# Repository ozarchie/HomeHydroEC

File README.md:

# HomeHydroEC
=============
An extension of Michael Ratcliffe's excellent EC project.   
<B>See the Project Wiki for a full description.  </B>  
https://github.com/ozarchie/HomeHydroEC/wiki  

## Extensions  
-------------
This project addresses the issue of polarization by implementing a square wave balanced resistor approach to measurement.  
An additional analog input channel is required.  
The 1k resistor is split in two as two 470R resistors and the probe inserted between the resistors.  
The voltage across the 470R sense resistor allows calculation of the sense current.  
The voltage across the prongs and the sense current allows determination of the electrical conductivity.  
An 18B20 sensor is connected to monitor the solution temperature.  

Testing and documentation is underway. Documentation is included in the code.  

The Kcell of the probe is calculated using standard formula and measurements of the AC probe. 
EC Measurements agree well with Chinese TDC&EC meters.  
See the Project Wiki for a full description.  

## Original Work  

Original ideas and program published by -:  

www.MichaelRatcliffe.com/projects  
https://www.element14.com/community/community/design-challenges/vertical-farming/blog/2015/09/13/automated-green-house-blogs-main-page  
 
  28/8/2015  Michael Ratcliffe  Mike@MichaelRatcliffe.com

   This program is free software: you can redistribute it and/or modify
    it under the terms of the GNU General Public License as published by
    the Free Software Foundation, either version 3 of the License, or
    (at your option) any later version.

    This program is distributed in the hope that it will be useful,
    but WITHOUT ANY WARRANTY; without even the implied warranty of
    MERCHANTABILITY or FITNESS FOR A PARTICULAR PURPOSE.  See the
    GNU General Public License for more details.

    You should have received a copy of the GNU General Public License
    along with this program.  If not, see <http://www.gnu.org/licenses/>.

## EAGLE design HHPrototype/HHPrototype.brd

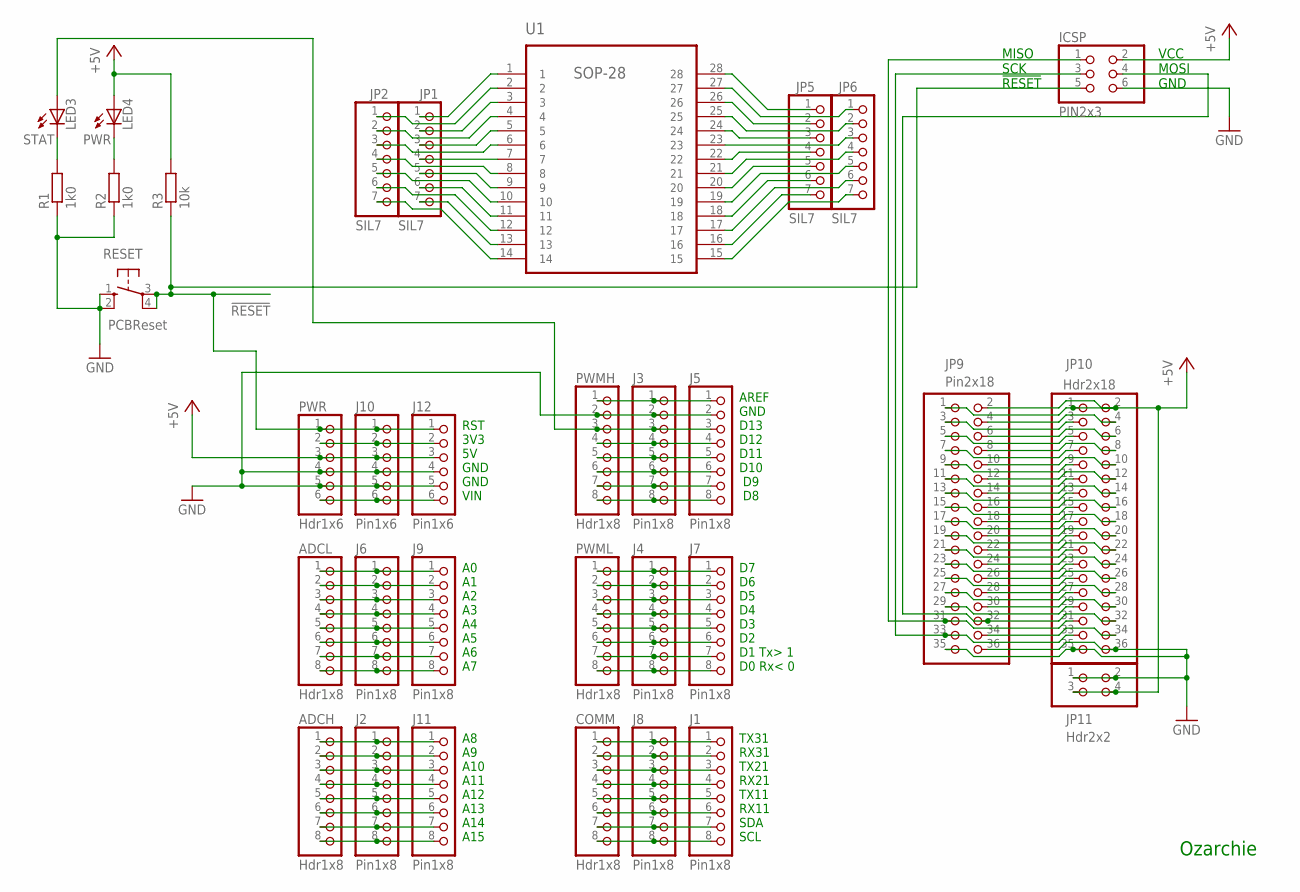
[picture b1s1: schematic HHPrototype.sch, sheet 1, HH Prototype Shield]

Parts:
ADCH: Hdr1x8; 1X08
ADCL: Hdr1x8; 1X08
COMM: Hdr1x8; 1X08
ICSP: PIN2x3; 2X03
J1, J2, J3, J4, J5, J6, J7, J8, J9, J11: Pin1x8; 1X08
J10, J12: Pin1x6; 1X06
JP1, JP2, JP5, JP6: SIL7; 1X07
JP9: Pin2x18; 2X18
JP10: Hdr2x18; 2X18
JP11: Hdr2x2; 2X02
LED3: STAT; CHIPLED_1206
LED4: PWR; CHIPLED_1206
PWMH: Hdr1x8; 1X08
PWML: Hdr1x8; 1X08
PWR: Hdr1x6; 1X06
R1, R2: 1k0; R0805
R3: 10k; R0805
RESET: PCBReset; B3F-10XX
U1: SOP-28; SOP50P1030X264-28N

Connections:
3V3: J10.2, J12.2, PWR.2
!RESET!: ICSP.5, J10.1, J12.1, PWR.1, R3.1, RESET.3, RESET.4 (P1)
+5V: ICSP.2, J10.3, J12.3, JP9.1, JP9.2, JP10.1, JP10.2, JP11.3, JP11.4, LED4.A, PWR.3, R3.2; also elsewhere on the board
A0: ADCL.1, J6.1, J9.1
A1: ADCL.2, J6.2, J9.2
A2: ADCL.3, J6.3, J9.3
A3: ADCL.4, J6.4, J9.4
A4: ADCL.5, J6.5, J9.5
A5: ADCL.6, J6.6, J9.6
A6: ADCL.7, J6.7, J9.7
A7: ADCL.8, J6.8, J9.8
A8: ADCH.1, J2.1, J11.1
A9: ADCH.2, J2.2, J11.2
A10: ADCH.3, J2.3, J11.3
A11: ADCH.4, J2.4, J11.4
A12: ADCH.5, J2.5, J11.5
A13: ADCH.6, J2.6, J11.6
A14: ADCH.7, J2.7, J11.7
A15: ADCH.8, J2.8, J11.8
AREF: J3.1, J5.1, PWMH.1
D0/RX0: J4.8, J7.8, PWML.8
D1/TX0: J4.7, J7.7, PWML.7
D2PWM: J4.6, J7.6, PWML.6
D3PWM: J4.5, J7.5, PWML.5
D4PWM: J4.4, J7.4, PWML.4
D5PWM: J4.3, J7.3, PWML.3
D6PWM: J4.2, J7.2, PWML.2
D7PWM: J4.1, J7.1, PWML.1
D8PWM: J3.8, J5.8, PWMH.8
D9PWM: J3.7, J5.7, PWMH.7
D10PWM: J3.6, J5.6, PWMH.6
D11PWM: J3.5, J5.5, PWMH.5
D12PWM: J3.4, J5.4, PWMH.4
D13PWM: J3.3, J5.3, LED3.A, PWMH.3
D14/TX3: COMM.1, J1.1, J8.1
D15/RX3: COMM.2, J1.2, J8.2
D16/TX2: COMM.3, J1.3, J8.3
D17/RX2: COMM.4, J1.4, J8.4
D18/TX1: COMM.5, J1.5, J8.5
D19/RX1: COMM.6, J1.6, J8.6
D20/SDA: COMM.7, J1.7, J8.7
D21/SCL: COMM.8, J1.8, J8.8
D22: JP9.3, JP10.3
D23: JP9.4, JP10.4
D24: JP9.5, JP10.5
D25: JP9.6, JP10.6
D26: JP9.7, JP10.7
D27: JP9.8, JP10.8
D28: JP9.9, JP10.9
D29: JP9.10, JP10.10
D30: JP9.11, JP10.11
D31: JP9.12, JP10.12
D32: JP9.13, JP10.13
D33: JP9.14, JP10.14
D34: JP9.15, JP10.15
D35: JP9.16, JP10.16
D36: JP9.17, JP10.17
D37: JP9.18, JP10.18
D38: JP9.19, JP10.19
D39: JP9.20, JP10.20
D40: JP9.21, JP10.21
D41: JP9.22, JP10.22
D42: JP9.23, JP10.23
D43: JP9.24, JP10.24
D44: JP9.25, JP10.25
D45: JP9.26, JP10.26
D46: JP9.27, JP10.27
D47: JP9.28, JP10.28
D48: JP9.29, JP10.29
D49: JP9.30, JP10.30
D53: JP9.34, JP10.34
GND: ICSP.6, J3.2, J5.2, J10.4, J10.5, J12.4, J12.5, JP9.35, JP9.36, JP10.35, JP10.36, JP11.1, JP11.2, PWMH.2, PWR.4, PWR.5, R1.1, R2.1, RESET.1 (S), RESET.2 (S1); also elsewhere on the board
MISO: ICSP.1, JP9.31, JP10.31
MOSI: ICSP.4, JP9.32, JP10.32
unnamed: LED3.C, R1.2
unnamed: LED4.C, R2.2
SCK: ICSP.3, JP9.33, JP10.33
SO1: JP1.1, U1.1
SO2: JP2.1, U1.2
SO3: JP1.2, U1.3
SO4: JP2.2, U1.4
SO5: JP1.3, U1.5
SO6: JP2.3, U1.6
SO7: JP1.4, U1.7
SO8: JP2.4, U1.8
SO9: JP1.5, U1.9
SO10: JP2.5, U1.10
SO11: JP1.6, U1.11
SO12: JP2.6, U1.12
SO13: JP1.7, U1.13
SO14: JP2.7, U1.14
SO15: JP6.7, U1.15
SO16: JP5.7, U1.16
SO17: JP6.6, U1.17
SO18: JP5.6, U1.18
SO19: JP6.5, U1.19
SO20: JP5.5, U1.20
SO21: JP6.4, U1.21
SO22: JP5.4, U1.22
SO23: JP6.3, U1.23
SO24: JP5.3, U1.24
SO25: JP6.2, U1.25
SO26: JP5.2, U1.26
SO27: JP6.1, U1.27
SO28: JP5.1, U1.28
VIN: J10.6, J12.6, PWR.6

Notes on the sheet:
RST 3V3 5V GND GND VIN
MISO SCK !RESET!
VCC MOSI GND
AREF GND D13 D12 D11 D10 D9 D8
D7 D6 D5 D4 D3 D2 D1 Tx> 1 D0 Rx< 0
A0 A1 A2 A3 A4 A5 A6 A7
A8 A9 A10 A11 A12 A13 A14 A15
TX31 RX31 TX21 RX21 TX11 RX11 SDA SCL
Ozarchie

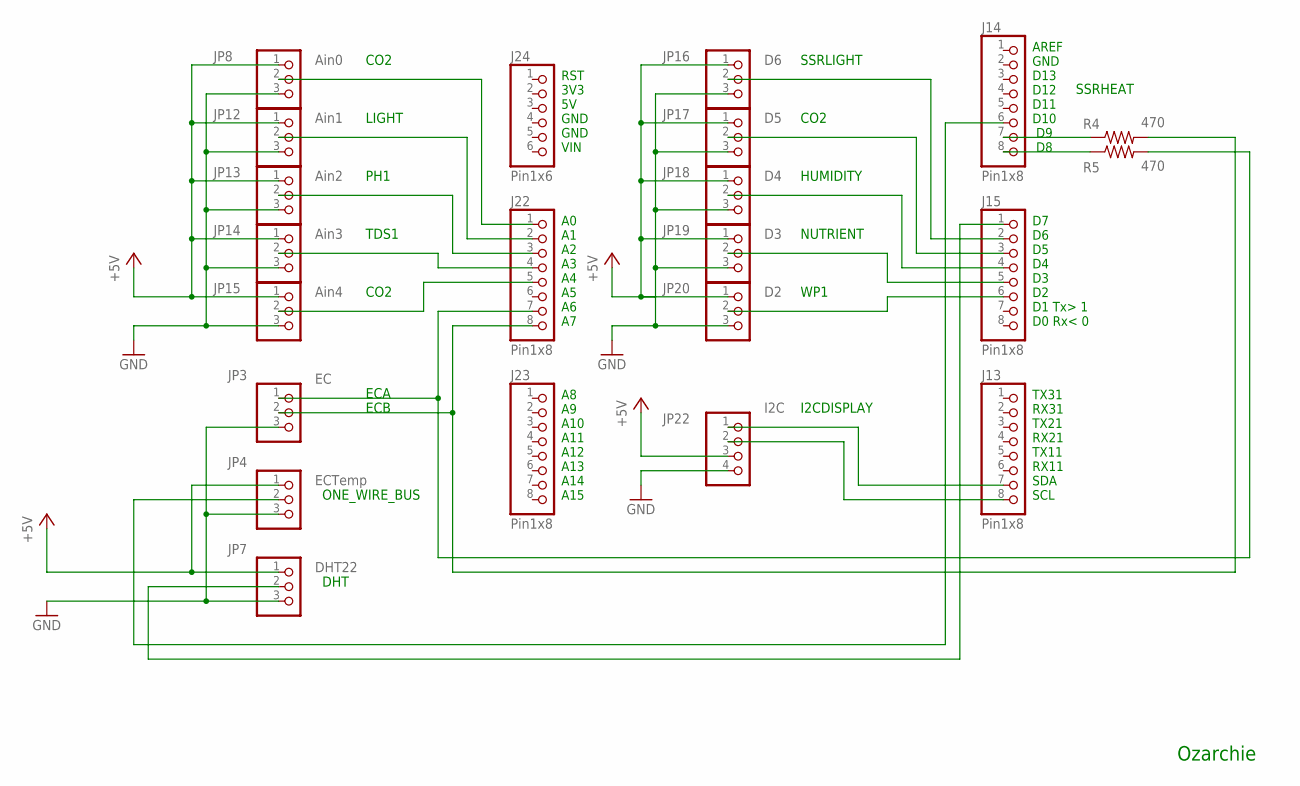
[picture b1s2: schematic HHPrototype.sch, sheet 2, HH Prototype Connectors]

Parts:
J13, J14, J15, J22, J23: Pin1x8; 1X08
J24: Pin1x6; 1X06
JP3: EC; 1X03
JP4: ECTemp; 1X03
JP7: DHT22; 1X03
JP8: Ain0; 1X03
JP12: Ain1; 1X03
JP13: Ain2; 1X03
JP14: Ain3; 1X03
JP15: Ain4; 1X03
JP16: D6; 1X03
JP17: D5; 1X03
JP18: D4; 1X03
JP19: D3; 1X03
JP20: D2; 1X03
JP22: I2C; 1X04
R4, R5: 470; 0207/2V

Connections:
+5V: JP4.1, JP7.1, JP8.1, JP12.1, JP13.1, JP14.1, JP15.1, JP16.1, JP17.1, JP18.1, JP19.1, JP20.1, JP22.3; also elsewhere on the board
GND: JP3.3, JP4.3, JP7.3, JP8.3, JP12.3, JP13.3, JP14.3, JP15.3, JP16.3, JP17.3, JP18.3, JP19.3, JP20.3, JP22.4; also elsewhere on the board
unnamed: J22.7, JP3.1, R5.2
unnamed: J15.6, JP20.2
unnamed: J15.5, JP19.2
unnamed: J15.4, JP18.2
unnamed: J15.3, JP17.2
unnamed: J15.2, JP16.2
unnamed: J22.1, JP8.2
unnamed: J22.2, JP12.2
unnamed: J22.3, JP13.2
unnamed: J22.4, JP14.2
unnamed: J22.5, JP15.2
unnamed: J13.7, JP22.1
unnamed: J13.8, JP22.2
unnamed: J15.1, JP7.2
unnamed: J22.8, JP3.2, R4.2
unnamed: J14.7, R4.1
unnamed: J14.6, JP4.2
unnamed: J14.8, R5.1

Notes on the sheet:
RST 3V3 5V GND GND VIN
A0 A1 A2 A3 A4 A5 A6 A7
A8 A9 A10 A11 A12 A13 A14 A15
Ozarchie
AREF GND D13 D12 D11 D10 D9 D8
D7 D6 D5 D4 D3 D2 D1 Tx> 1 D0 Rx< 0
TX31 RX31 TX21 RX21 TX11 RX11 SDA SCL
CO2
LIGHT
PH1
TDS1
ECA
ECB
SSRLIGHT
HUMIDITY
NUTRIENT
WP1
SSRHEAT
ONE_WIRE_BUS
DHT
I2CDISPLAY

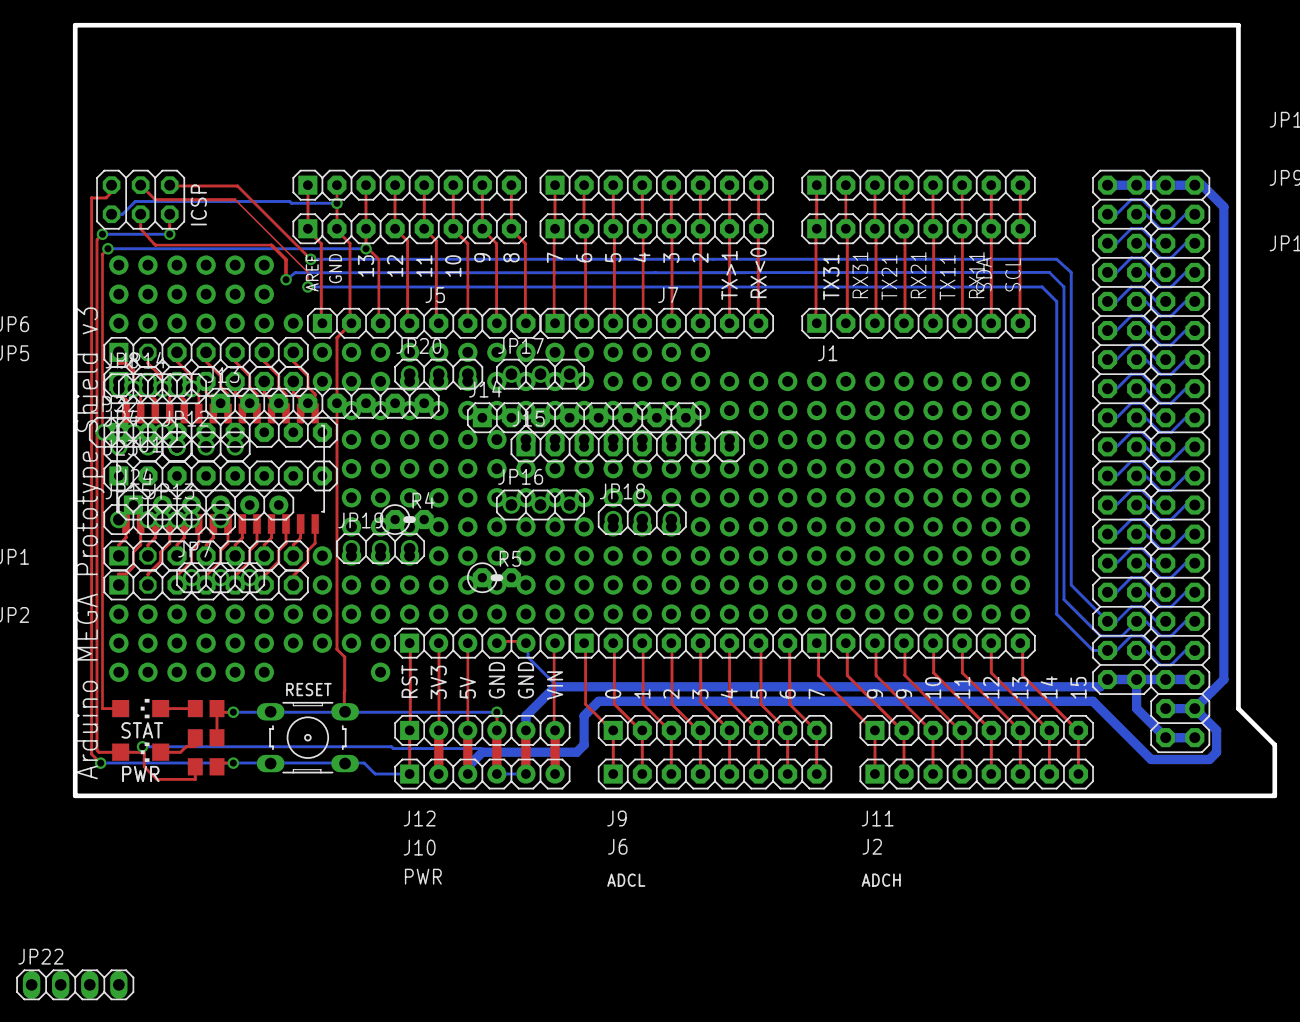
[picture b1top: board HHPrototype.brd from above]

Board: 2 copper layers, 104.8 x 67.3 mm, 55 parts (0 on the bottom side), 124 nets.

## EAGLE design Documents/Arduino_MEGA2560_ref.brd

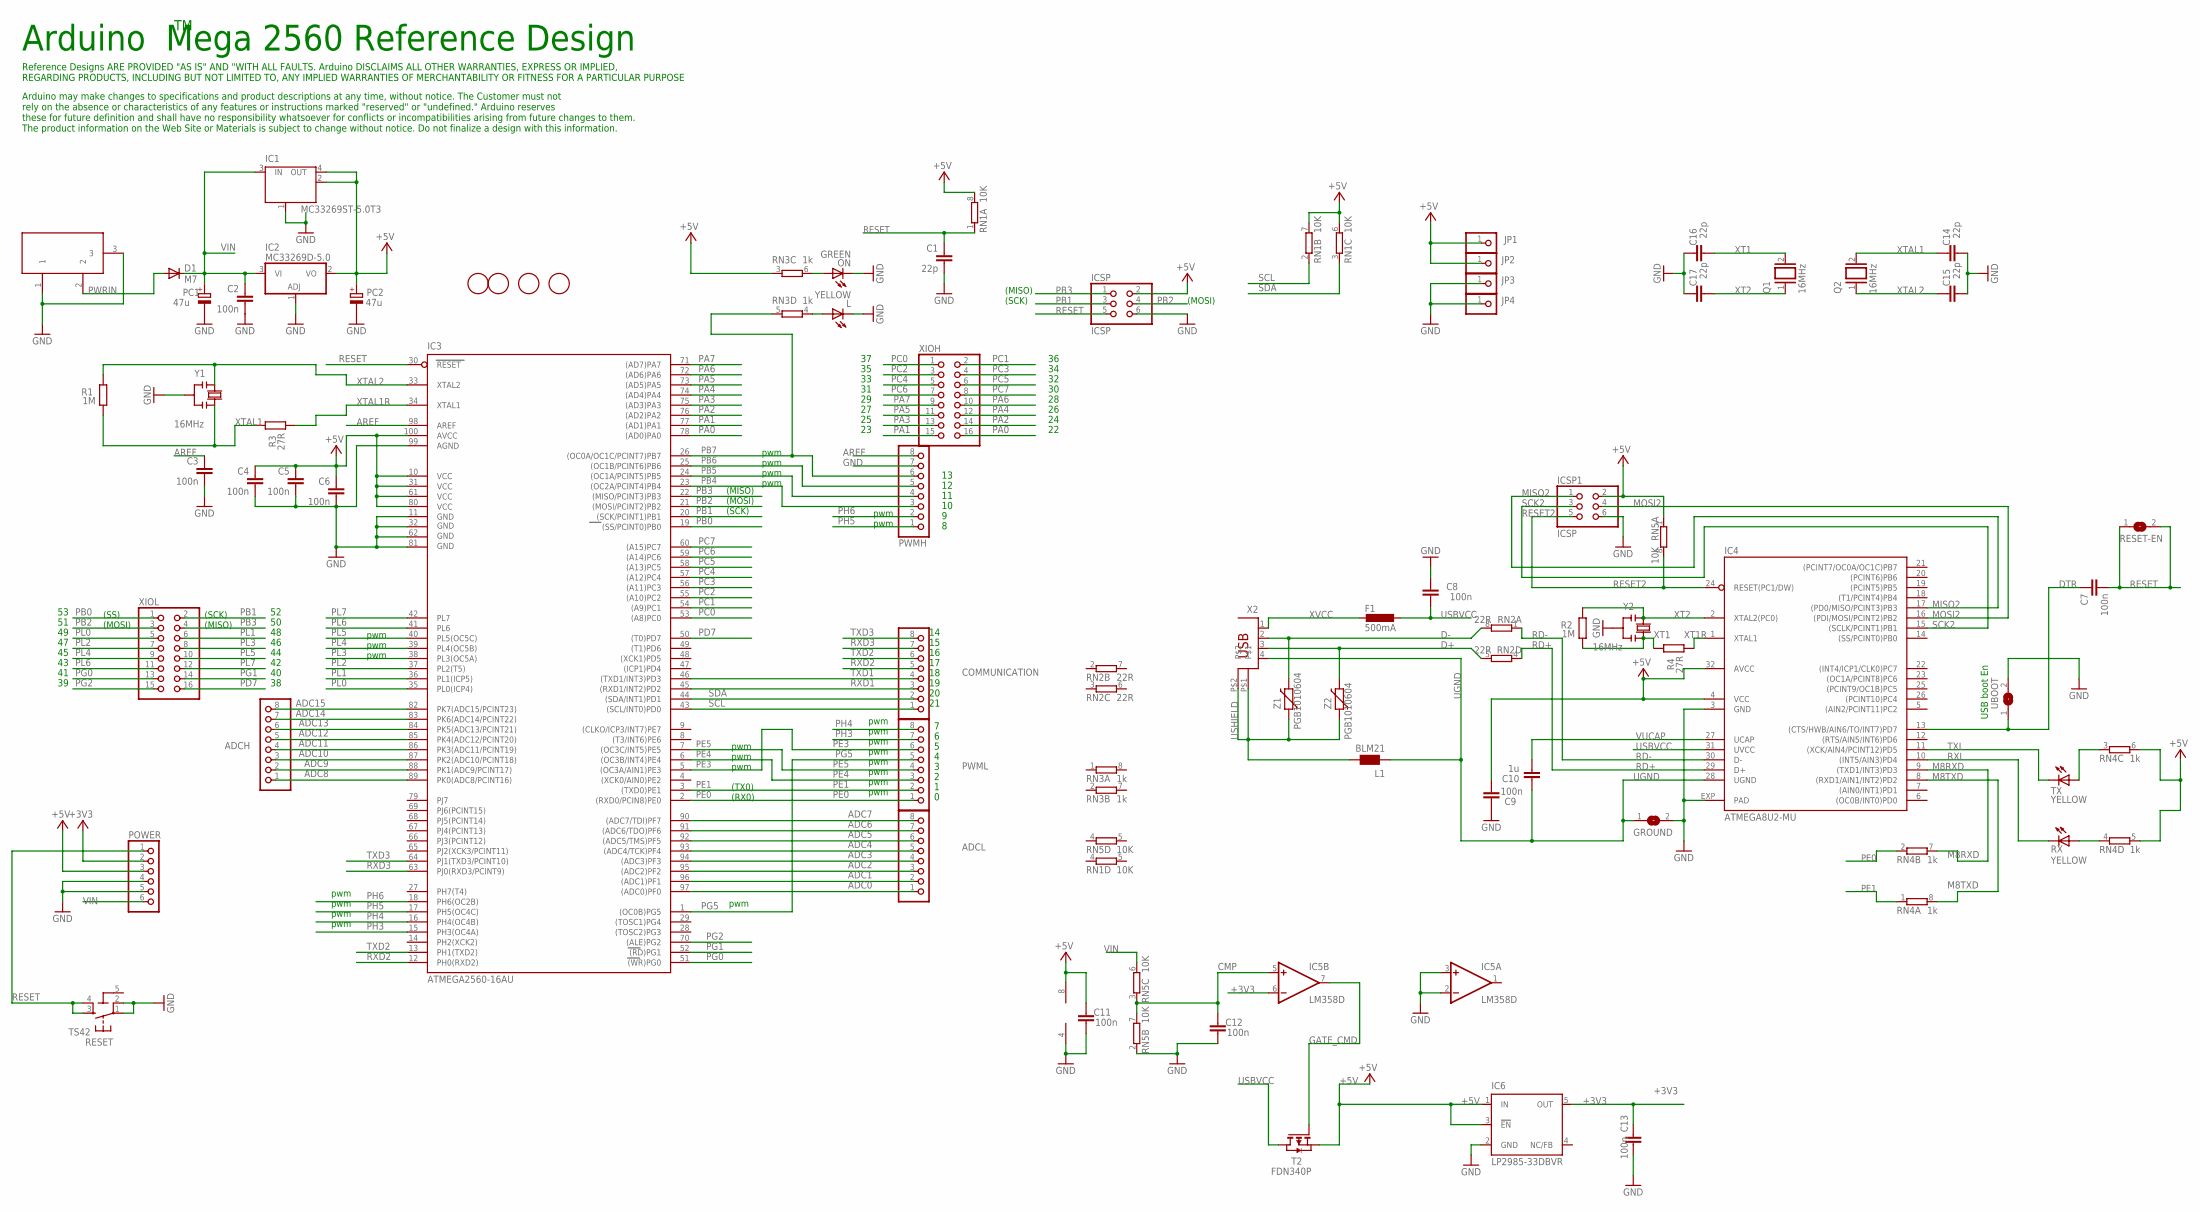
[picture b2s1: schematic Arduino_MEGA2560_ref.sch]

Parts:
ADCH: PINHD-1X8; 1X08
ADCL: PINHD-1X8; 1X08
C1, C14, C15, C16, C17: 22p; C0603-ROUND
C2, C3, C4, C5, C6, C7, C9, C12, C13: 100n; C0603-ROUND
C8, C11: 100n; C0603
C10: 1u; C0603-ROUND
COMMUNICATION: PINHD-1X8; 1X08
D1: M7; SMB
F1: 500mA; L1812
GROUND: SJ
IC1: MC33269ST-5.0T3; SOT223
IC2: MC33269D-5.0; DPACK
IC3: ATMEGA2560-16AU; TQFP100
IC4: ATMEGA8U2-MU; QFN32
IC5: LM358D; SO08
IC6: LP2985-33DBVR; SOT23-DBV
ICSP, ICSP1: ICSP; 2X03
JP1, JP2, JP3, JP4: PINHD-1X1; 1X01
L: YELLOW; CHIP-LED0805
L1: BLM21; 0805
ON: GREEN; CHIP-LED0805
PC1, PC2: 47u; PANASONIC_D
POWER: PINHD-1X6; 1X06
PWMH: PINHD-1X8; 1X08
PWML: PINHD-1X8; 1X08
Q1, Q2: 16MHz; QS
R1, R2: 1M; R0603-ROUND
R3, R4: 27R; R0603-ROUND
RESET: TS42
RESET-EN: SJ
RN1, RN5: 10K; CAT16
RN2: 22R; CAY16
RN3, RN4: 1k; CAY16
RX: YELLOW; CHIP-LED0805
T2: FDN340P; SOT-23
TX: YELLOW; CHIP-LED0805
U$2, U$3, U$4, U$5: FIDUCIALMOUNT; FIDUCIA-MOUNT
UBOOT: SJ
X1: DC21MMX; DC-21MM
X2: PN61729
XIOH: PINHD-2X8; 2X08
XIOL: PINHD-2X8; 2X08
Y1, Y2: 16MHz; RESONATOR
Z1, Z2: PGB1010604; CT/CN0603

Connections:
5-GND: RESET.5 (5-GND)
+3V3: C13.2, IC5.6 (-IN), IC6.5 (OUT), POWER.2
+5V: C4.1, C5.1, C6.1, C9.1, C11.2, IC1.2 (OUT), IC1.4 (OUT), IC2.2 (VO), IC3.10 (VCC), IC3.31 (VCC1), IC3.61 (VCC2), IC3.80 (VCC3), IC3.100 (AVCC), IC4.4 (VCC), IC4.32 (AVCC), IC5.8 (V+), IC6.1 (IN), IC6.3 (!EN), ICSP.2, ICSP1.2, JP1.1, JP2.1, PC2.+, POWER.3, RN1.6 (2), RN1.7 (2), RN1.8 (2), RN3.3 (1), RN4.5 (2), RN4.6 (2), RN5.1, T2.2 (S)
ADC0: ADCL.1, IC3.97 ((ADC0)PF0)
ADC1: ADCL.2, IC3.96 ((ADC1)PF1)
ADC2: ADCL.3, IC3.95 ((ADC2)PF2)
ADC3: ADCL.4, IC3.94 ((ADC3)PF3)
ADC4: ADCL.5, IC3.93 ((ADC4/TCK)PF4)
ADC5: ADCL.6, IC3.92 ((ADC5/TMS)PF5)
ADC6: ADCL.7, IC3.91 ((ADC6/TDO)PF6)
ADC7: ADCL.8, IC3.90 ((ADC7/TDI)PF7)
ADC8: ADCH.1, IC3.89 (PK0(ADC8/PCINT16))
ADC9: ADCH.2, IC3.88 (PK1(ADC9/PCINT17))
ADC10: ADCH.3, IC3.87 (PK2(ADC10/PCINT18))
ADC11: ADCH.4, IC3.86 (PK3(ADC11/PCINT19))
ADC12: ADCH.5, IC3.85 (PK4(ADC12/PCINT20))
ADC13: ADCH.6, IC3.84 (PK5(ADC13/PCINT21))
ADC14: ADCH.7, IC3.83 (PK6(ADC14/PCINT22))
ADC15: ADCH.8, IC3.82 (PK7(ADC15/PCINT23))
AREF: C3.1, IC3.98 (AREF), PWMH.8
CMP: C12.2, IC5.5 (+IN), RN5.3 (1), RN5.7 (2)
D+: RN2.5 (2), X2.3, Z2.2
D-: RN2.8 (2), X2.2, Z1.2
DTR: C7.1, IC4.13 ((CTS/HWB/AIN6/TO/INT7)PD7), UBOOT.1
GATE_CMD: IC5.7 (OUT), T2.3 (G)
GND: C1.2, C2.2, C3.2, C4.2, C5.2, C6.2, C8.2, C9.2, C11.1, C12.1, C13.1, C14.1, C15.1, C16.2, C17.2, GROUND.2, IC1.1 (GND/ADJ), IC2.1 (ADJ), IC3.11 (GND), IC3.32 (GND1), IC3.62 (GND2), IC3.81 (GND3), IC3.99 (AGND), IC4.3 (GND), IC4.EXP (PAD), IC5.2 (-IN), IC5.3 (+IN), IC5.4 (V-), IC6.2 (GND), ICSP.6, ICSP1.6, JP3.1, JP4.1, L.C, ON.C, PC1.-, PC2.-, POWER.4, POWER.5, PWMH.7, RESET.1, RESET.2, RN5.2 (1), UBOOT.2, X1.1, X1.3, Y1.2, Y2.2
M8RXD: IC4.9 ((TXD1/INT3)PD3), RN4.7 (2)
M8TXD: IC4.8 ((RXD1/AIN1/INT2)PD2), RN4.8 (2)
MISO2: IC4.17 ((PD0/MISO/PCINT3)PB3), ICSP1.1
MOSI2: IC4.16 ((PDI/MOSI/PCINT2)PB2), ICSP1.4
unnamed: L.A, RN3.4 (1)
unnamed: ON.A, RN3.6 (2)
unnamed: RN4.4 (1), RX.A
unnamed: RN4.3 (1), TX.A
PA0: IC3.78 ((AD0)PA0), XIOH.16
PA1: IC3.77 ((AD1)PA1), XIOH.15
PA2: IC3.76 ((AD2)PA2), XIOH.14
PA3: IC3.75 ((AD3)PA3), XIOH.13
PA4: IC3.74 ((AD4)PA4), XIOH.12
PA5: IC3.73 ((AD5)PA5), XIOH.11
PA6: IC3.72 ((AD6)PA6), XIOH.10
PA7: IC3.71 ((AD7)PA7), XIOH.9
PB0: IC3.19 ((SS/PCINT0)PB0), XIOL.1
PB1: IC3.20 ((SCK/PCINT1)PB1), ICSP.3, XIOL.2
PB2: IC3.21 ((MOSI/PCINT2)PB2), ICSP.4, XIOL.3
PB3: IC3.22 ((MISO/PCINT3)PB3), ICSP.1, XIOL.4
PB4: IC3.23 ((OC2A/PCINT4)PB4), PWMH.3
PB5: IC3.24 ((OC1A/PCINT5)PB5), PWMH.4
PB6: IC3.25 ((OC1B/PCINT6)PB6), PWMH.5
PB7: IC3.26 ((OC0A/OC1C/PCINT7)PB7), PWMH.6, RN3.5 (2)
PC0: IC3.53 ((A8)PC0), XIOH.1
PC1: IC3.54 ((A9)PC1), XIOH.2
PC2: IC3.55 ((A10)PC2), XIOH.3
PC3: IC3.56 ((A11)PC3), XIOH.4
PC4: IC3.57 ((A12)PC4), XIOH.5
PC5: IC3.58 ((A13)PC5), XIOH.6
PC6: IC3.59 ((A14)PC6), XIOH.7
PC7: IC3.60 ((A15)PC7), XIOH.8
PD7: IC3.50 ((T0)PD7), XIOL.16
PE0: IC3.2 ((RXD0/PCIN8)PE0), PWML.1, RN4.2 (1)
PE1: IC3.3 ((TXD0)PE1), PWML.2, RN4.1
PE3: IC3.5 ((OC3A/AIN1)PE3), PWML.6
PE4: IC3.6 ((OC3B/INT4)PE4), PWML.3
PE5: IC3.7 ((OC3C/INT5)PE5), PWML.4
PG0: IC3.51 ((WR)PG0), XIOL.13
PG1: IC3.52 ((RD)PG1), XIOL.14
PG2: IC3.70 ((ALE)PG2), XIOL.15
PG5: IC3.1 ((OC0B)PG5), PWML.5
PH3: IC3.15 (PH3(OC4A)), PWML.7
PH4: IC3.16 (PH4(OC4B)), PWML.8
PH5: IC3.17 (PH5(OC4C)), PWMH.1
PH6: IC3.18 (PH6(OC2B)), PWMH.2
PL0: IC3.35 (PL0(ICP4)), XIOL.5
PL1: IC3.36 (PL1(ICP5)), XIOL.6
PL2: IC3.37 (PL2(T5)), XIOL.7
PL3: IC3.38 (PL3(OC5A)), XIOL.8
PL4: IC3.39 (PL4(OC5B)), XIOL.9
PL5: IC3.40 (PL5(OC5C)), XIOL.10
PL6: IC3.41 (PL6), XIOL.11
PL7: IC3.42 (PL7), XIOL.12
PWRIN: D1.A, X1.2
RD+: IC4.29 (D+), RN2.4 (1)
RD-: IC4.30 (D-), RN2.1
RESET: C1.1, C7.2, IC3.30 (RESET), ICSP.5, POWER.1, RESET.3, RESET.4, RESET-EN.1, RESET-EN.2, RN1.1
RESET2: IC4.24 (RESET(PC1/DW)), ICSP1.5, RN5.8 (2)
RXD1: COMMUNICATION.3, IC3.45 ((RXD1/INT2)PD2)
RXD2: COMMUNICATION.5, IC3.12 (PH0(RXD2))
RXD3: COMMUNICATION.7, IC3.63 (PJ0(RXD3/PCINT9))
RXL: IC4.10 ((INT5/AIN3)PD4), RX.C
SCK2: IC4.15 ((SCLK/PCINT1)PB1), ICSP1.3
SCL: COMMUNICATION.1, IC3.43 ((SCL/INT0)PD0), RN1.2 (1)
SDA: COMMUNICATION.2, IC3.44 ((SDA/INT1)PD1), RN1.3 (1)
TXD1: COMMUNICATION.4, IC3.46 ((TXD1/INT3)PD3)
TXD2: COMMUNICATION.6, IC3.13 (PH1(TXD2))
TXD3: COMMUNICATION.8, IC3.64 (PJ1(TXD3/PCINT10))
TXL: IC4.11 ((XCK/AIN4/PCINT12)PD5), TX.C
UGND: C10.2, GROUND.1, IC4.28 (UGND), L1.1, X2.4
USBVCC: C8.1, F1.1, IC4.31 (UVCC), T2.1 (D)
USHIELD: L1.2, X2.P$1, X2.P$2, Z1.1, Z2.1
VIN: C2.1, D1.C, IC1.3 (IN), IC2.3 (VI), PC1.+, POWER.6, RN5.6 (2)
VUCAP: C10.1, IC4.27 (UCAP)
XT1: C16.1, Q1.2, R2.1, R4.2, Y2.3
XT1R: IC4.1 (XTAL1), R4.1
XT2: C17.1, IC4.2 (XTAL2(PC0)), Q1.1, R2.2, Y2.1
XTAL1: C14.2, Q2.2, R1.1, R3.2, Y1.3
XTAL1R: IC3.34 (XTAL1), R3.1
XTAL2: C15.2, IC3.33 (XTAL2), Q2.1, R1.2, Y1.1
XVCC: F1.2, X2.1

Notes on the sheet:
(SCK)
(MISO)
(MOSI)
pwm
(TX0)
(RX0)
(SS)
USB boot En
Arduino Mega 2560 Reference Design
Arduino may make changes to specifications and product descriptions at any time, without notice. The Customer must not rely on the absence or characteristics of any features or instructions marked "reserved" or "undefined." Arduino reserves these for future definition and shall have no responsibili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
Reference Designs ARE PROVIDED "AS IS" AND "WITH ALL FAULTS. Arduino DISCLAIMS ALL OTHER WARRANTIES, EXPRESS OR IMPLIED, REGARDING PRODUCTS, INCLUDING BUT NOT LIMITED TO, ANY IMPLIED WARRANTIES OF MERCHANTABILITY OR FITNESS FOR A PARTICULAR PURPOSE

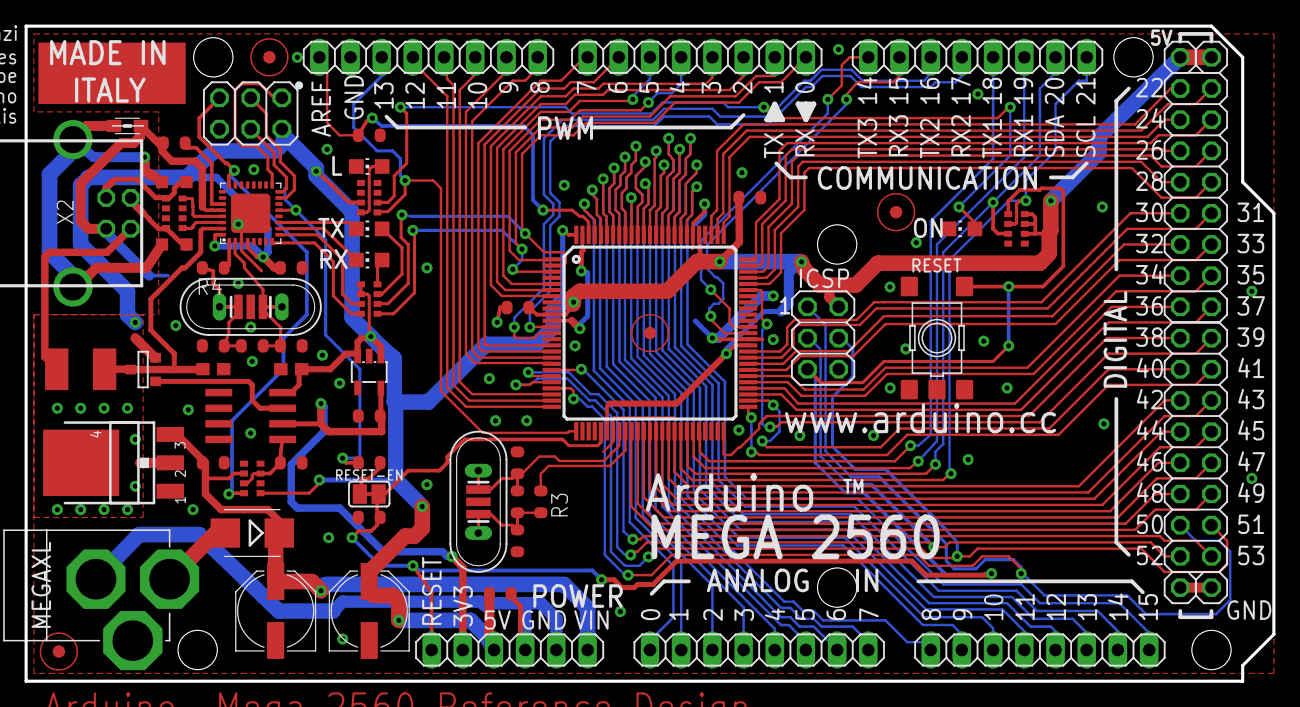
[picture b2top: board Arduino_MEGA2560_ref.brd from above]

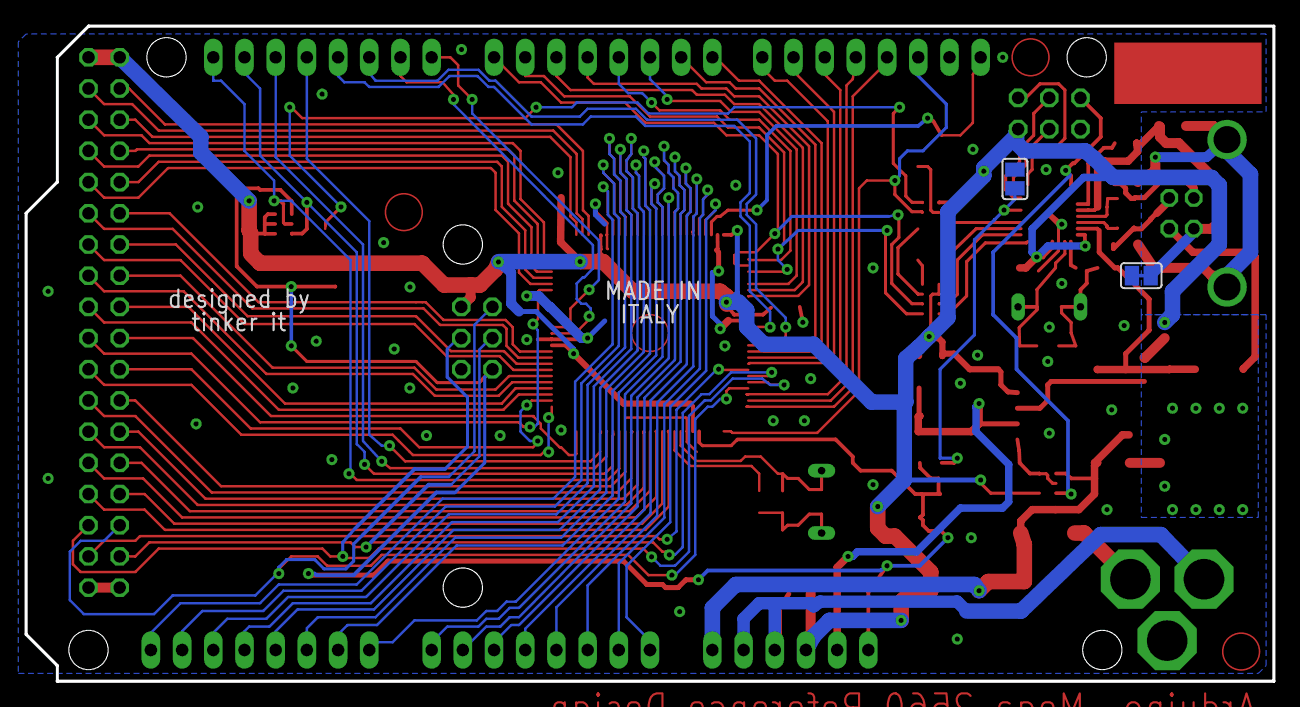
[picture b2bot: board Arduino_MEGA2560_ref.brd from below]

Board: 2 copper layers, 101.6 x 53.3 mm, 72 parts (2 on the bottom side), 107 nets.

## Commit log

2016-12-07 Initial rework of Michael Ratcliffe's code
    Rework to change mode of operation to ‘AC”.
    This required some changes to the hardware - documentation is under way.
    The code now has polarity, so that measurements do not polarise the
    solution.
    Testing is user way, with initial results comparing well with Chinese
    handheld devices.
2016-12-08 Update for Wiki
    Wiki and start of schematics
2016-12-08 Schematic for EC Sensor
2016-12-08 Add pdf
2020-01-01 Update for Home Hydro Project
    Uses the EC Sensor in a complete Home Hydro project

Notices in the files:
parts and their libraries:
pmc: Created by Ultra Librarian Gold 5.3.88 Copyright © 1999-2010
